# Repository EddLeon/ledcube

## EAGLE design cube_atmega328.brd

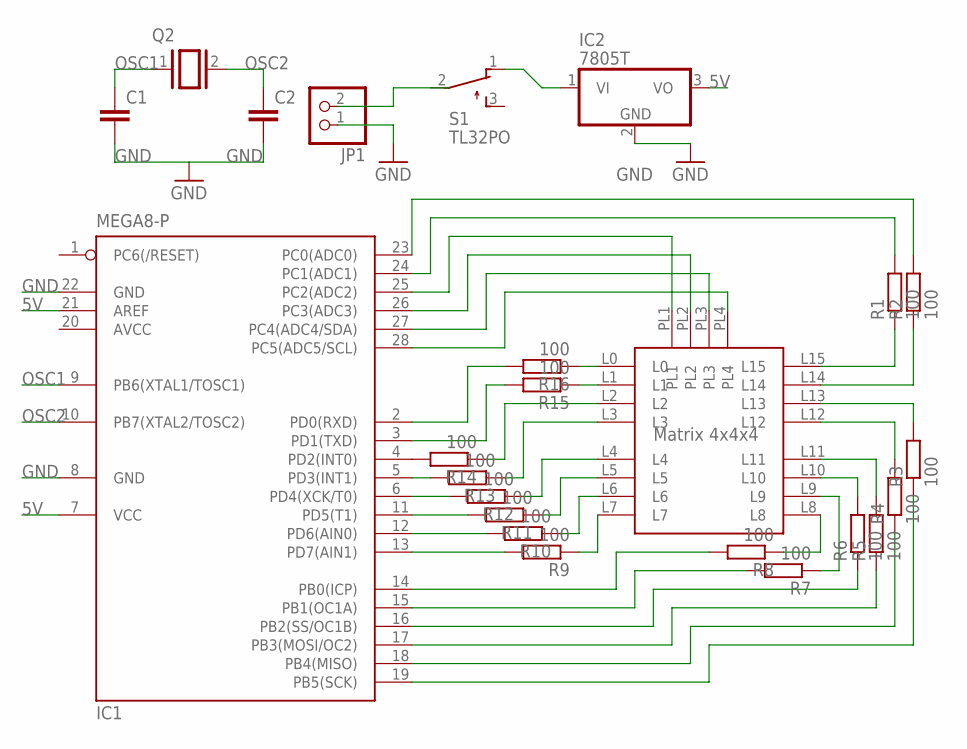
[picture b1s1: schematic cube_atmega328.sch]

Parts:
C1, C2: C5/2.5; C5B2.5
IC1: MEGA8-P; DIL28-3
IC2: 7805T; TO220H
JP1: PINHD-1X2; 1X02
Q2: XTAL/S; QS
R1, R2, R3, R4, R5, R6, R7, R8, R9, R10, R11, R12, R13, R14, R15, R16: 100; 0207/10
S1: TL32PO; TL3XPO
U$1: LC4X4X4

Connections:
5V: IC1.7 (VCC), IC1.21 (AREF), IC2.3 (VO)
AVCC: IC1.20 (AVCC)
GND: C1.2, C2.2, IC1.8 (GND), IC1.22 (GND), IC2.2 (GND), JP1.1
unnamed: IC1.2 (PD0(RXD)), R16.2
unnamed: IC1.3 (PD1(TXD)), R15.2
unnamed: R14.1, U$1.L2
unnamed: R13.1, U$1.L3
unnamed: R12.1, U$1.L4
unnamed: R11.1, U$1.L5
unnamed: R10.1, U$1.L6
unnamed: IC1.13 (PD7(AIN1)), R9.2
unnamed: IC1.14 (PB0(ICP)), R8.2
unnamed: IC1.15 (PB1(OC1A)), R7.2
unnamed: IC1.16 (PB2(SS/OC1B)), R6.1
unnamed: IC1.17 (PB3(MOSI/OC2)), R5.1
unnamed: IC1.18 (PB4(MISO)), R4.1
unnamed: IC1.19 (PB5(SCK)), R3.1
unnamed: IC1.23 (PC0(ADC0)), R2.2
unnamed: IC1.24 (PC1(ADC1)), R1.2
unnamed: IC1.25 (PC2(ADC2)), U$1.PL1
unnamed: IC1.26 (PC3(ADC3)), U$1.PL2
unnamed: IC1.27 (PC4(ADC4/SDA)), U$1.PL3
unnamed: IC1.28 (PC5(ADC5/SCL)), U$1.PL4
unnamed: R1.1, U$1.L15
unnamed: R2.1, U$1.L14
unnamed: R3.2, U$1.L13
unnamed: R4.2, U$1.L12
unnamed: R5.2, U$1.L11
unnamed: R6.2, U$1.L10
unnamed: R7.1, U$1.L9
unnamed: R8.1, U$1.L8
unnamed: R9.1, U$1.L7
unnamed: IC1.12 (PD6(AIN0)), R10.2
unnamed: IC1.11 (PD5(T1)), R11.2
unnamed: IC1.6 (PD4(XCK/T0)), R12.2
unnamed: IC1.5 (PD3(INT1)), R13.2
unnamed: IC1.4 (PD2(INT0)), R14.2
unnamed: R15.1, U$1.L1
unnamed: R16.1, U$1.L0
unnamed: IC2.1 (VI), S1.1 (O)
OSC1: C1.1, IC1.9 (PB6(XTAL1/TOSC1)), Q2.1
OSC2: C2.1, IC1.10 (PB7(XTAL2/TOSC2)), Q2.2

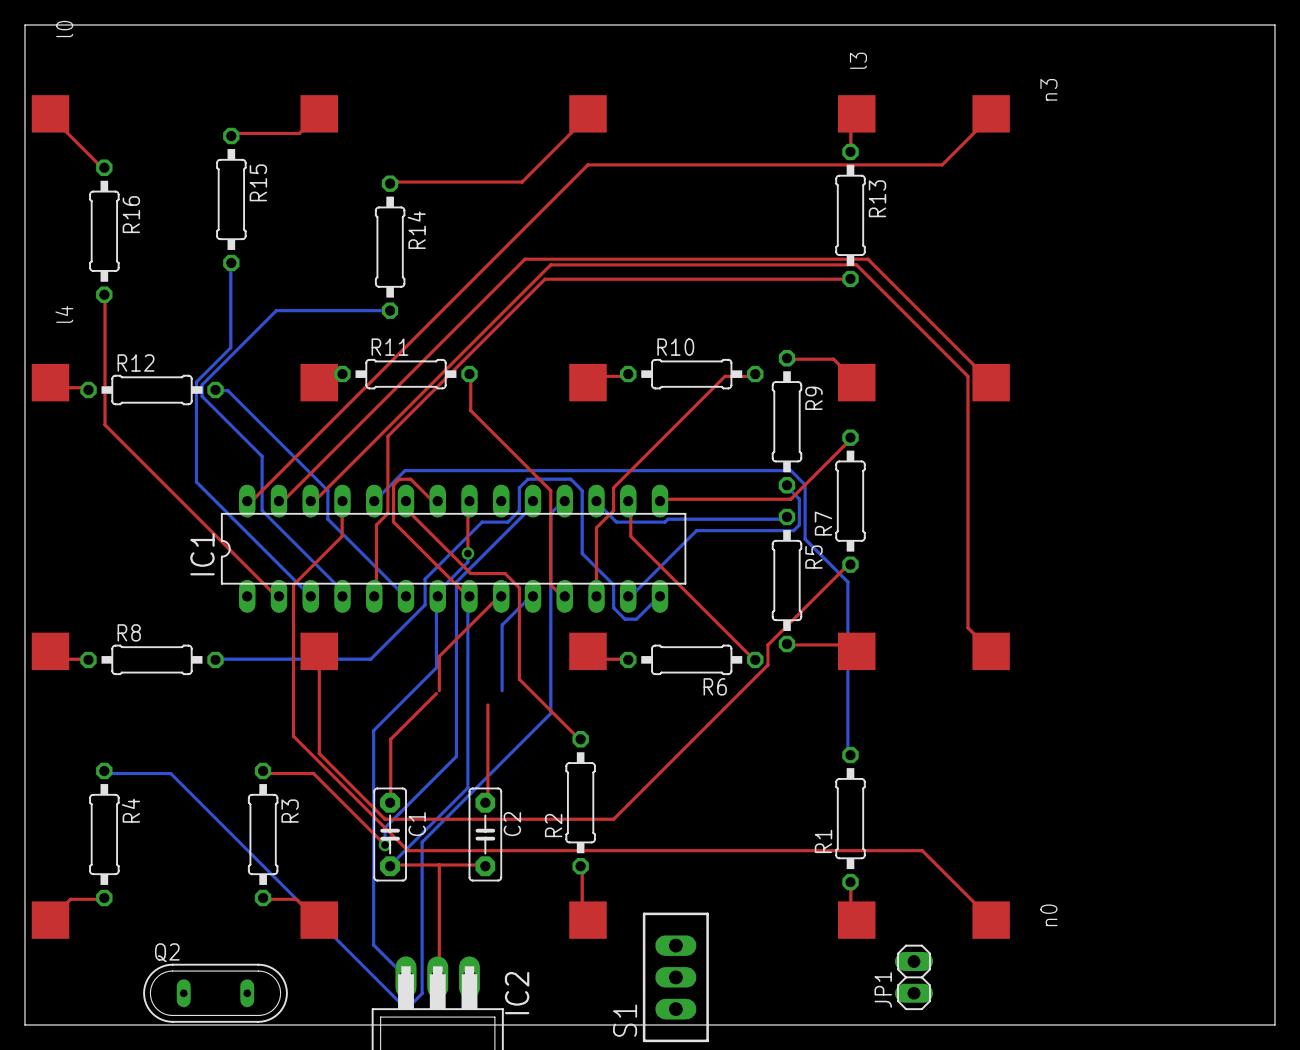
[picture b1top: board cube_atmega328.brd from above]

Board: 2 copper layers, 100.0 x 80.0 mm, 24 parts (0 on the bottom side), 41 nets.
